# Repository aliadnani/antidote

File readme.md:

Budget neural amp modelling on a Radxa Cubie A7Z.

---

[(sloppy demo video)](https://www.youtube.com/shorts/qqARMGN2HPs)

## What this project does

Neural Amp Modeler (NAM) uses neural networks to model guitar amplifiers from recorded input/output pairs, then reproduces their response on live guitar audio. I want to make a standalone guitar pedal for it.

Rust firmware runs on a Radxa Cubie A7Z Linux SBC. It manages real-time audio capture and playback, including the hot loop that processes each buffer, wraps NAM A2’s C++ DSP library via FFI, and coordinates model loading and the pedal’s peripherals. A custom audio board provides instrument-level input and output.

The end goal is a budget, performant, standalone NAM pedal targetting buffers processed in under 10 ms (ideally under 5 ms) - essentially the threshold for human auditory latency perception.

## This repo

- `src/`: Rust firmware for audio processing, NAM A2 FFI, model loading, and pedal controls.
- `hardware/`: Schematics and PCB design files for the audio board + associated Linux device tree overlays

**Please see this repository as more of a reference design for what's possible and how such a pedal could be built, rather than a polished product.**

## Hardware setup

1. Source a Radxa Cubie A7Z
   - Note: other similar SBCs (like the Pi Zero/OrangePis/etc.) likely **will not work** due to different GPIO header pinouts
2. Have the audio board fabricated with all components populated.
3. Connect the audio board to the SBC via the 40-pin GPIO header.
4. Connect other peripherals to the audio board. In my case, I connected (and built my firmware around):
   - 3.5mm headphone jack for phones
   - 6.35mm TS input for guitar
   - 6.35mm TS output for amp
   - A single footswitch
   - An I2C OLED display (SH1106)
   - A WS2812B LED strip

## Firmware setup

1. Flash the SBC with Linux. Official Radxa images or community Armbian images should work fine.
2. Compile and load the driver for the audio board's codec (TAC5112).
   - See the [TI git repository](https://git.ti.com/cgit/lpaa-android-drivers/tac5x1x-linux-driver/?h=tac5x1x_driver) for the source. Check out a branch or tag compatible with your kernel version.
   - Run `make`, then load the kernel module with `insmod` or `modprobe`.
3. Compile and load the device tree overlay for the audio board.
   - The source is `./hardware/tac5112_i2c_i2s_overlay.dts`. Compile it with `dtc` into a `.dtbo` file, then load it via `rsetup`.
4. Configure the codec's ADC, DAC, and capture/playback paths if needed. These commands may be needed:
   ```sh
   sudo amixer -c 0 cset name='ASI_RX_CH1_EN Switch' on
   sudo amixer -c 0 cset name='OUT1x Source' 'DAC Input'
   sudo amixer -c 0 cset name='OUT1x Config' 'Pseudo differential with OUTxM as VCOM'
   sudo amixer -c 0 cset name='OUT1x Driver' 'Headphone'

   sudo amixer -c 0 cset name='ASI_RX_CH2_EN Switch' on
   sudo amixer -c 0 cset name='OUT2x Source' 'DAC Input'
   sudo amixer -c 0 cset name='OUT2x Config' 'Mono Single-ended at OUTxP only'
   sudo amixer -c 0 cset name='OUT2x Driver' 'Line-out'

   sudo amixer -c 0 cset name='ADC1 Config' 'Single-ended'
   sudo amixer -c 0 cset name='ADC1 Common-mode Tolerance' 'AC Coupled with 100mVpp'
   sudo amixer -c 0 cset name='ADC1 Full-Scale' '2/10-VRMS'
   sudo amixer -c 0 cset name='ASI_TX_CH1 Slot' 'Slot0'
   sudo amixer -c 0 cset name='ASI_TX_CH1_EN Capture Switch' on
   sudo amixer -c 0 cset name='ADC1 Digital Capture Volume' 161

   sudo amixer -c 0 cset name='IN1 Source Mux' 'Analog'
   sudo amixer -c 0 cset name='IN2 Source Mux' 'Analog'
   ```
5. Pull in the dependencies, then build the firmware in release mode on the SBC or cross-compile it on a host:
   ```sh
   git submodule update --init --recursive
   cargo build --release
   ```
6. Run the firmware in release mode, passing the directory containing your `.nam` models. If omitted, it uses `resources/`:
   ```sh
   ./target/release/antidote /path/to/nam/files
   # Or:
   cargo run --release -- /path/to/nam/files
   ```

   ```text
   2026-09-25T16:57:33.860341Z  INFO antidote: Starting Antidote.
   2026-09-25T16:57:33.880659Z  INFO antidote::modeller: Loaded NAM A2 model. model_path=resources/fender_brown.nam
   2026-09-25T16:57:33.880875Z  INFO antidote: Starting CPAL.
   2026-09-25T16:57:33.989547Z  INFO antidote: Playing back audio for 500 seconds.
   2026-09-25T16:57:34.898597Z  INFO antidote::audio: Audio errors input_drops=0 output_drops=0 output_underruns=320
   2026-09-25T16:57:35.898842Z  INFO antidote::audio: Audio errors input_drops=0 output_drops=0 output_underruns=320
   2026-09-25T16:57:36.899102Z  INFO antidote::audio: Audio errors input_drops=0 output_drops=0 output_underruns=320
   ...
   ```

## Polishing touches

Once everything is working, some things you can do to make the pedal more usable:

- Add a `systemd` service to run the firmware on boot

### Optimizations

- Disable all unnecessary kernel modules to reduce boot time
  - Stock boots in around ~20 seconds which is actually pretty good - but you can cut another 5-10
- If using a `6.12+` kernel, you can use the play with the `PREEMPT_RT` to reduce latency
- Play around with `mlockall` and `threadirqs`, core pinning/isolation. You can push buffer sizes to around ~24 this way yielding a theorical round-trip latency of ~2ms. 

## Some design goals/notes:

In principle, this project actually builds an entire hardware platform for *any* real-time guitar processing application for Linux SBCs. You can just as easily swap out the the firmware for another that runs say LV2/VST plugins. Though the main focus for this project is a standalone NAM pedal.

---

Built on top of:

- [NAM A2 Source Code](https://github.com/sdatkinson/NeuralAmpModelerCore)
- [NAM A2 Reference](https://www.tone3000.com/guides/nam-a2-the-complete-guide)

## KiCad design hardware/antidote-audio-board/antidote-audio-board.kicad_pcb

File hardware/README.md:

# Hardware

This directory contains hardware-related files for the Antidote project, including schematics, PCB layouts, and other stuff.

So far we have:
- `antidote-audio-board/`: KiCAD project for the Antidote audio board.
  - See `antidote-audio-board/schematic.pdf` for a PDF of the schematic.
- `tac5112_i2c_i2s_overlay.dts`: The overlay so we can actually bring up the TAC5112 audio codec on our Radxa Cubie A7Z.

## Audio Bring Up on the Radxa Cubie A7Z

Assuming:
- The TAC5112 (daughter-board) is connected via the GPIO headers
- The TAC5112 drivers are compiled and loaded as a module
  - For kernel: 5.15: https://git.ti.com/cgit/lpaa-android-drivers/tac5x1x-linux-driver/log/?h=tac5x1x_driver_k5.15
- The device overlay is compiled and loaded (e.g. via rsetup)

**To play a test tone:**
```bash
# Left channel (for mono headphones - same signal bridged at T/R pins)
# Not sure if `sudo` is needed to be honest
sudo amixer -c 0 cset name='ASI_RX_CH1_EN Switch' on
sudo amixer -c 0 cset name='OUT1x Source' 'DAC Input'
sudo amixer -c 0 cset name='OUT1x Config' 'Pseudo differential with OUTxM as VCOM'
sudo amixer -c 0 cset name='OUT1x Driver' 'Headphone'

# Right channel for instrument line out
sudo amixer -c 0 cset name='ASI_RX_CH2_EN Switch' on
sudo amixer -c 0 cset name='OUT2x Source' 'DAC Input'
sudo amixer -c 0 cset name='OUT2x Config' 'Mono Single-ended at OUTxP only'
sudo amixer -c 0 cset name='OUT2x Driver' 'Line-out'

speaker-test -D hw:0,0 -c 2 -r 48000 -F S32_LE -t sine -f 440
```

**To record audio (+generate spectrogram and log metrics):**
```bash
sudo amixer -c 0 cset name='ADC1 Config' 'Single-ended'
sudo amixer -c 0 cset name='ADC1 Common-mode Tolerance' 'AC Coupled with 100mVpp'
sudo amixer -c 0 cset name='ADC1 Full-Scale' '2/10-VRMS'
sudo amixer -c 0 cset name='ASI_TX_CH1 Slot' 'Slot0'
sudo amixer -c 0 cset name='ASI_TX_CH1_EN Capture Switch' on
sudo amixer -c 0 cset name='ADC1 Digital Capture Volume' 161

sudo amixer -c 0 cset name='IN1 Source Mux' 'Analog'
sudo amixer -c 0 cset name='IN2 Source Mux' 'Analog'

arecord -D hw:0,0 -c 2 -f S32_LE -r 48000 -d 5 retest.wav
sox retest.wav -n stat
sox retest.wav -n spectrogram -o retest_spectro.png
```

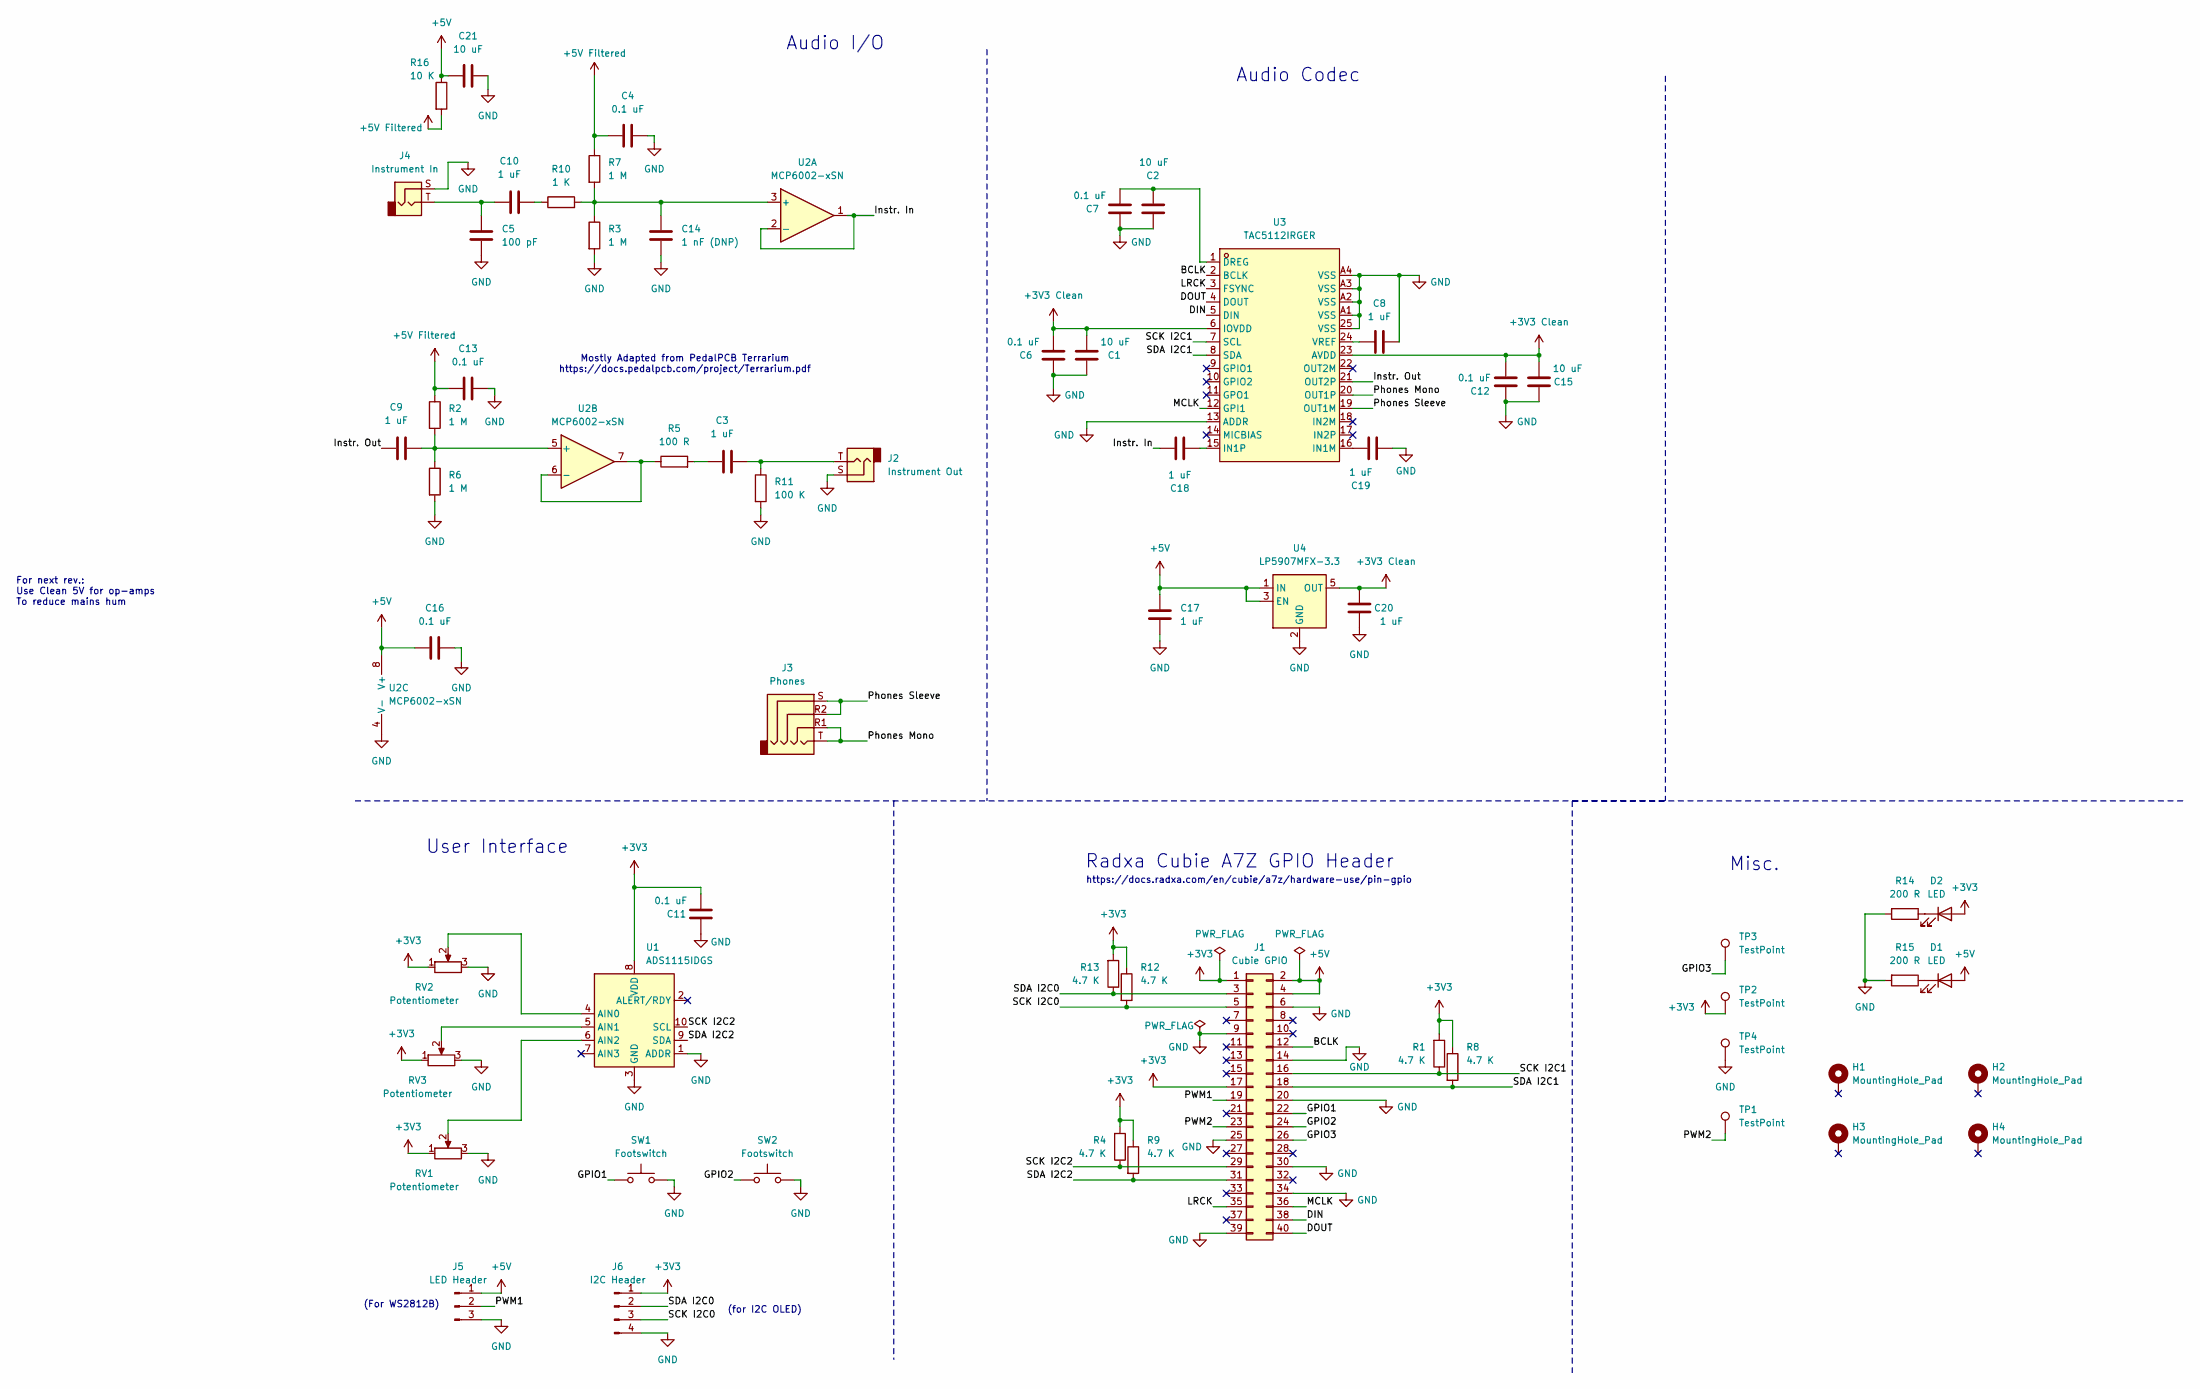
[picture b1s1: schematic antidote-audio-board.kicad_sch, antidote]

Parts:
C1, C2, C15, C21: 10 uF; C_0603_1608Metric
C3, C8, C9, C10, C17, C18, C19, C20: 1 uF; C_0603_1608Metric
C4, C6, C7, C11, C12, C13, C16: 0.1 uF; C_0603_1608Metric
C5: 100 pF; C_0603_1608Metric
C14: 1 nF (DNP); C_0603_1608Metric
D1, D2: LED; LED_0805_2012Metric
H1, H2, H3, H4: MountingHole_Pad; MountingHole_2.7mm_M2.5_Pad
J1: Cubie GPIO; PinHeader_2x20_P2.54mm_Vertical
J2: Instrument Out; SolderWire-0.5sqmm_1x02_P4.6mm_D0.9mm_OD2.1mm
J3: Phones; Jack_3.5mm_PJ320E_Horizontal
J4: Instrument In; SolderWire-0.5sqmm_1x02_P4.6mm_D0.9mm_OD2.1mm
J5: LED Header; PinHeader_1x03_P2.54mm_Vertical
J6: I2C Header; PinHeader_1x04_P2.54mm_Vertical
R1, R4, R8, R9, R12, R13: 4.7 K; R_0805_2012Metric
R2, R3, R6, R7: 1 M; R_0805_2012Metric
R5: 100 R; R_0805_2012Metric
R10: 1 K; R_0805_2012Metric
R11: 100 K; R_0805_2012Metric
R14, R15: 200 R; R_0805_2012Metric
R16: 10 K; R_0805_2012Metric
RV1, RV2, RV3: Potentiometer; PinHeader_1x03_P2.54mm_Vertical
SW1, SW2: Footswitch; PinHeader_1x02_P2.54mm_Vertical
TP1, TP2, TP3, TP4: TestPoint; TestPoint_Pad_1.5x1.5mm
U1: ADS1115IDGS; TSSOP-10_3x3mm_P0.5mm
U2: MCP6002-xSN; SOIC-8_3.9x4.9mm_P1.27mm
U3: TAC5112IRGER; VQFN-24_L4.0-W4.0-P0.50-BL-EP2.1_1; MPN TAC5112IRGER; LCSC Part C44853692
U4: LP5907MFX-3.3; SOT-23-5

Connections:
+3V3: C11.2, D2.2 (A), J1.1, J1.17, J6.1, R1.2, R4.2, R8.1, R9.1, R12.1, R13.2, RV1.1, RV2.1, RV3.1, TP2.1 (1_1), U1.8 (VDD)
+3V3 Clean: C1.2, C6.2, C12.2, C15.2, C20.1, U3.6 (IOVDD), U3.23 (AVDD), U4.5 (OUT)
+5V: C16.1, C17.1, C21.2, D1.2 (A), J1.2, J1.4, J5.1, R16.1, U2.8 (V+), U4.1 (IN), U4.3 (EN)
+5V Filtered: C4.1, C13.1, R2.1, R7.1, R16.2
/BCLK: J1.12, U3.2 (BCLK)
/DIN: J1.38, U3.5 (DIN)
/DOUT: J1.40, U3.4 (DOUT)
/GPIO1: J1.22, SW1.1
/GPIO2: J1.24, SW2.1
/GPIO3: J1.26, TP3.1 (1_1)
/Instr. In: C18.2, U2.1, U2.2 (-)
/Instr. Out: C9.1, U3.21 (OUT2P)
/LRCK: J1.35, U3.3 (FSYNC)
/MCLK: J1.36, U3.12 (GPI1)
/PWM1: J1.19, J5.2
/PWM2: J1.23, TP1.1 (1_1)
/Phones Mono: J3.R1, J3.T, U3.20 (OUT1P)
/Phones Sleeve: J3.R2, J3.S, U3.19 (OUT1M)
/SCK I2C0: J1.5, J6.3, R12.2
/SCK I2C1: J1.16, R1.1, U3.7 (SCL)
/SCK I2C2: J1.29, R4.1, U1.10 (SCL)
/SDA I2C0: J1.3, J6.2, R13.1
/SDA I2C1: J1.18, R8.2, U3.8 (SDA)
/SDA I2C2: J1.31, R9.2, U1.9 (SDA)
GND: C1.1, C2.1, C4.2, C5.2, C6.1, C7.1, C8.2, C11.1, C12.1, C13.2, C14.2, C15.1, C16.2, C17.2, C19.1, C20.2, C21.1, J1.6, J1.9, J1.14, J1.20, J1.25, J1.30, J1.34, J1.39, J2.S, J4.S, J5.3, J6.4, R3.2, R6.2, R11.2, R14.2, R15.2, RV1.3, RV2.3, RV3.3, SW1.2, SW2.2, TP4.1 (1_1), U1.1 (ADDR), U1.3 (GND), U2.4 (V-), U3.13 (ADDR), U3.25 (VSS), U3.A1 (VSS), U3.A2 (VSS), U3.A3 (VSS), U3.A4 (VSS), U4.2 (GND)
unnamed: C3.1, R5.2
unnamed: C3.2, J2.T, R11.1
unnamed: C5.1, C10.1, J4.T
unnamed: C10.2, R10.1
unnamed: D1.1 (K), R15.1
unnamed: D2.1 (K), R14.1
unnamed: RV2.2, U1.4 (AIN0)
unnamed: RV3.2, U1.5 (AIN1)
unnamed: RV1.2, U1.6 (AIN2)
unnamed: C14.1, R3.1, R7.2, R10.2, U2.3 (+)
unnamed: C9.2, R2.2, R6.1, U2.5 (+)
unnamed: R5.1, U2.6 (-), U2.7
unnamed: C2.2, C7.2, U3.1 (DREG)
unnamed: C19.2, U3.16 (IN1M)
unnamed: C18.1, U3.15 (IN1P)
unnamed: C8.1, U3.24 (VREF)

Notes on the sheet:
Audio Codec
Misc.
Mostly Adapted from PedalPCB Terrarium https://docs.pedalpcb.com/project/Terrarium.pdf
User Interface
Audio I/O
(For WS2812B)
For next rev.: Use Clean 5V for op-amps To reduce mains hum
https://docs.radxa.com/en/cubie/a7z/hardware-use/pin-gpio
Radxa Cubie A7Z GPIO Header
(for I2C OLED)

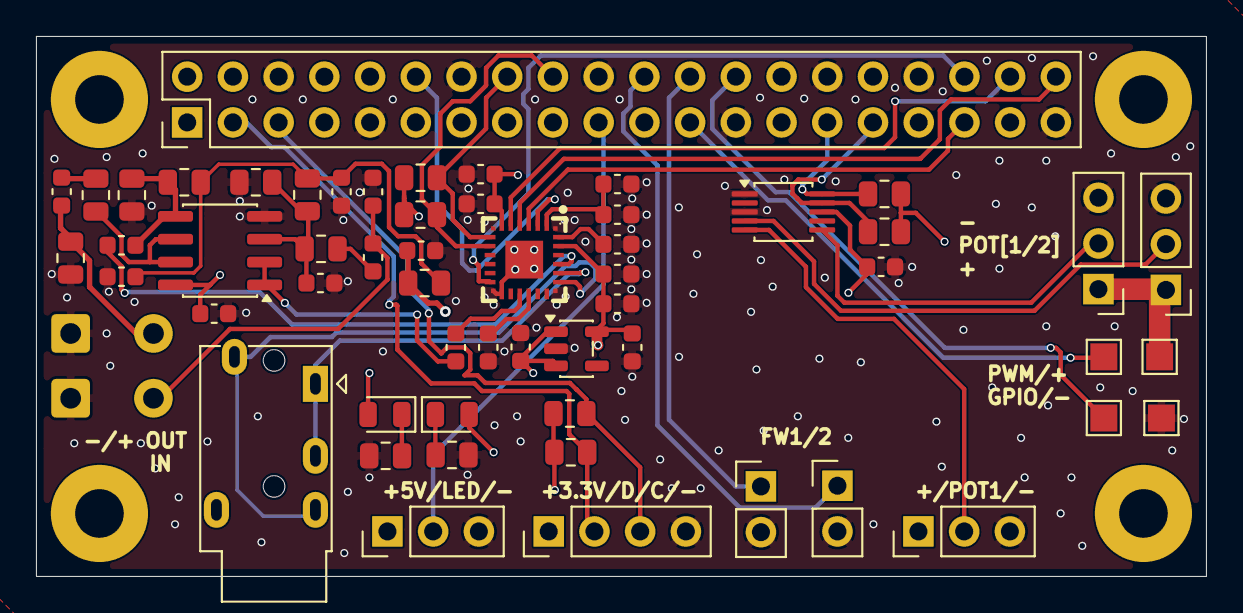
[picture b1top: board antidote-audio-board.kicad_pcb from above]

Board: 4 copper layers, 65.0 x 30.0 mm, 62 parts (0 on the bottom side), 41 nets.

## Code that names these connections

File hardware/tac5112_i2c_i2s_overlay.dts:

/dts-v1/;
/plugin/;

/ {
	metadata {
		title = "TAC5112 on TWI4 + I2S0 (standalone, replaces i2s0-2ch) V9";
		compatible = "radxa,cubie-a7z";
		category = "misc";
		exclusive = "twi4", "i2s0_plat", "i2s0_mach", "PJ24", "PJ25",
			    "PB4", "PB5", "PB6", "PB7", "PB8";
		description = "Full TAC5112 bring-up: TWI4 control bus (PJ24/PJ25) plus I2S0 audio bus (PB4-PB8) with the codec wired directly into soundcard-mach. Do NOT load alongside sun60iw2p1-i2s0-2ch.dtbo - this overlay replaces it.";
	};
};

&pio {
	twi4_pins_default: twi4-pins-default {
		pins = "PJ24", "PJ25";
		function = "twi4";
		drive-strength = <10>;
		bias-pull-up;
	};

	twi4_pins_sleep: twi4-pins-sleep {
		pins = "PJ24", "PJ25";
		function = "gpio_in";
	};

	i2s0_pins_mclk: i2s0-pins-mclk {
		pins = "PB4";
		function = "i2s0_mclk";
		allwinner,drive = <1>;
		bias-disable;
	};

	i2s0_pins_bclk: i2s0-pins-bclk {
		pins = "PB5";
		function = "i2s0_bclk";
		allwinner,drive = <1>;
		bias-disable;
	};

	i2s0_pins_lrck: i2s0-pins-lrck {
		pins = "PB6";
		function = "i2s0_lrck";
		allwinner,drive = <1>;
		bias-disable;
	};

	i2s0_pins_din0: i2s0-pins-din1 {
		pins = "PB7";
		function = "i2s0_din1";
		allwinner,drive = <1>;
		bias-disable;
	};

	i2s0_pins_dout0: i2s0-pins-dout1 {
		pins = "PB8";
		function = "i2s0_dout1";
		allwinner,drive = <1>;
		bias-disable;
	};

	i2s0_pins_sleep: i2s0-pins-sleep {
		pins = "PB4", "PB5", "PB6", "PB8", "PB7";
		function = "io_disabled";
		allwinner,drive = <1>;
		bias-disable;
	};
};

&twi4 {
	clock-frequency = <400000>;
	pinctrl-0 = <&twi4_pins_default>;
	pinctrl-1 = <&twi4_pins_sleep>;
	pinctrl-names = "default", "sleep";
	status = "okay";

	tac5112: audio-codec@50 {
		compatible = "ti,tac5112";
		reg = <0x50>;
		#sound-dai-cells = <0>;
		ti,vref = <0>;
		ti,micbias-vg = <0>;
	};
};

&i2s0_plat {
	tdm-num = <0>;
	tx-pin = <1>;
	rx-pin = <1>;

	rxfifo-pinmap = <1 1>;
	rxfifo-chmap = <0 1>;

	tx-hub-en;
	rx-sync-en;
	pinctrl-used;
	pinctrl-names = "default", "sleep";
	pinctrl-0 = <&i2s0_pins_mclk &i2s0_pins_bclk &i2s0_pins_lrck
		     &i2s0_pins_din0 &i2s0_pins_dout0>;
	pinctrl-1 = <&i2s0_pins_sleep>;
	status = "okay";
};

&i2s0_mach {
	soundcard-mach,format = "i2s";
	soundcard-mach,slot-num = <2>;
	soundcard-mach,slot-width = <32>;
	soundcard-mach,frame-master = <&i2s0_cpu>;
	soundcard-mach,bitclock-master = <&i2s0_cpu>;
	status = "okay";

	i2s0_cpu: soundcard-mach,cpu {
		sound-dai = <&i2s0_plat>;
		soundcard-mach,pll-fs = <1>;
		soundcard-mach,mclk-fs = <256>;
	};

	soundcard-mach,codec {
		sound-dai = <&tac5112>;
	};
};
